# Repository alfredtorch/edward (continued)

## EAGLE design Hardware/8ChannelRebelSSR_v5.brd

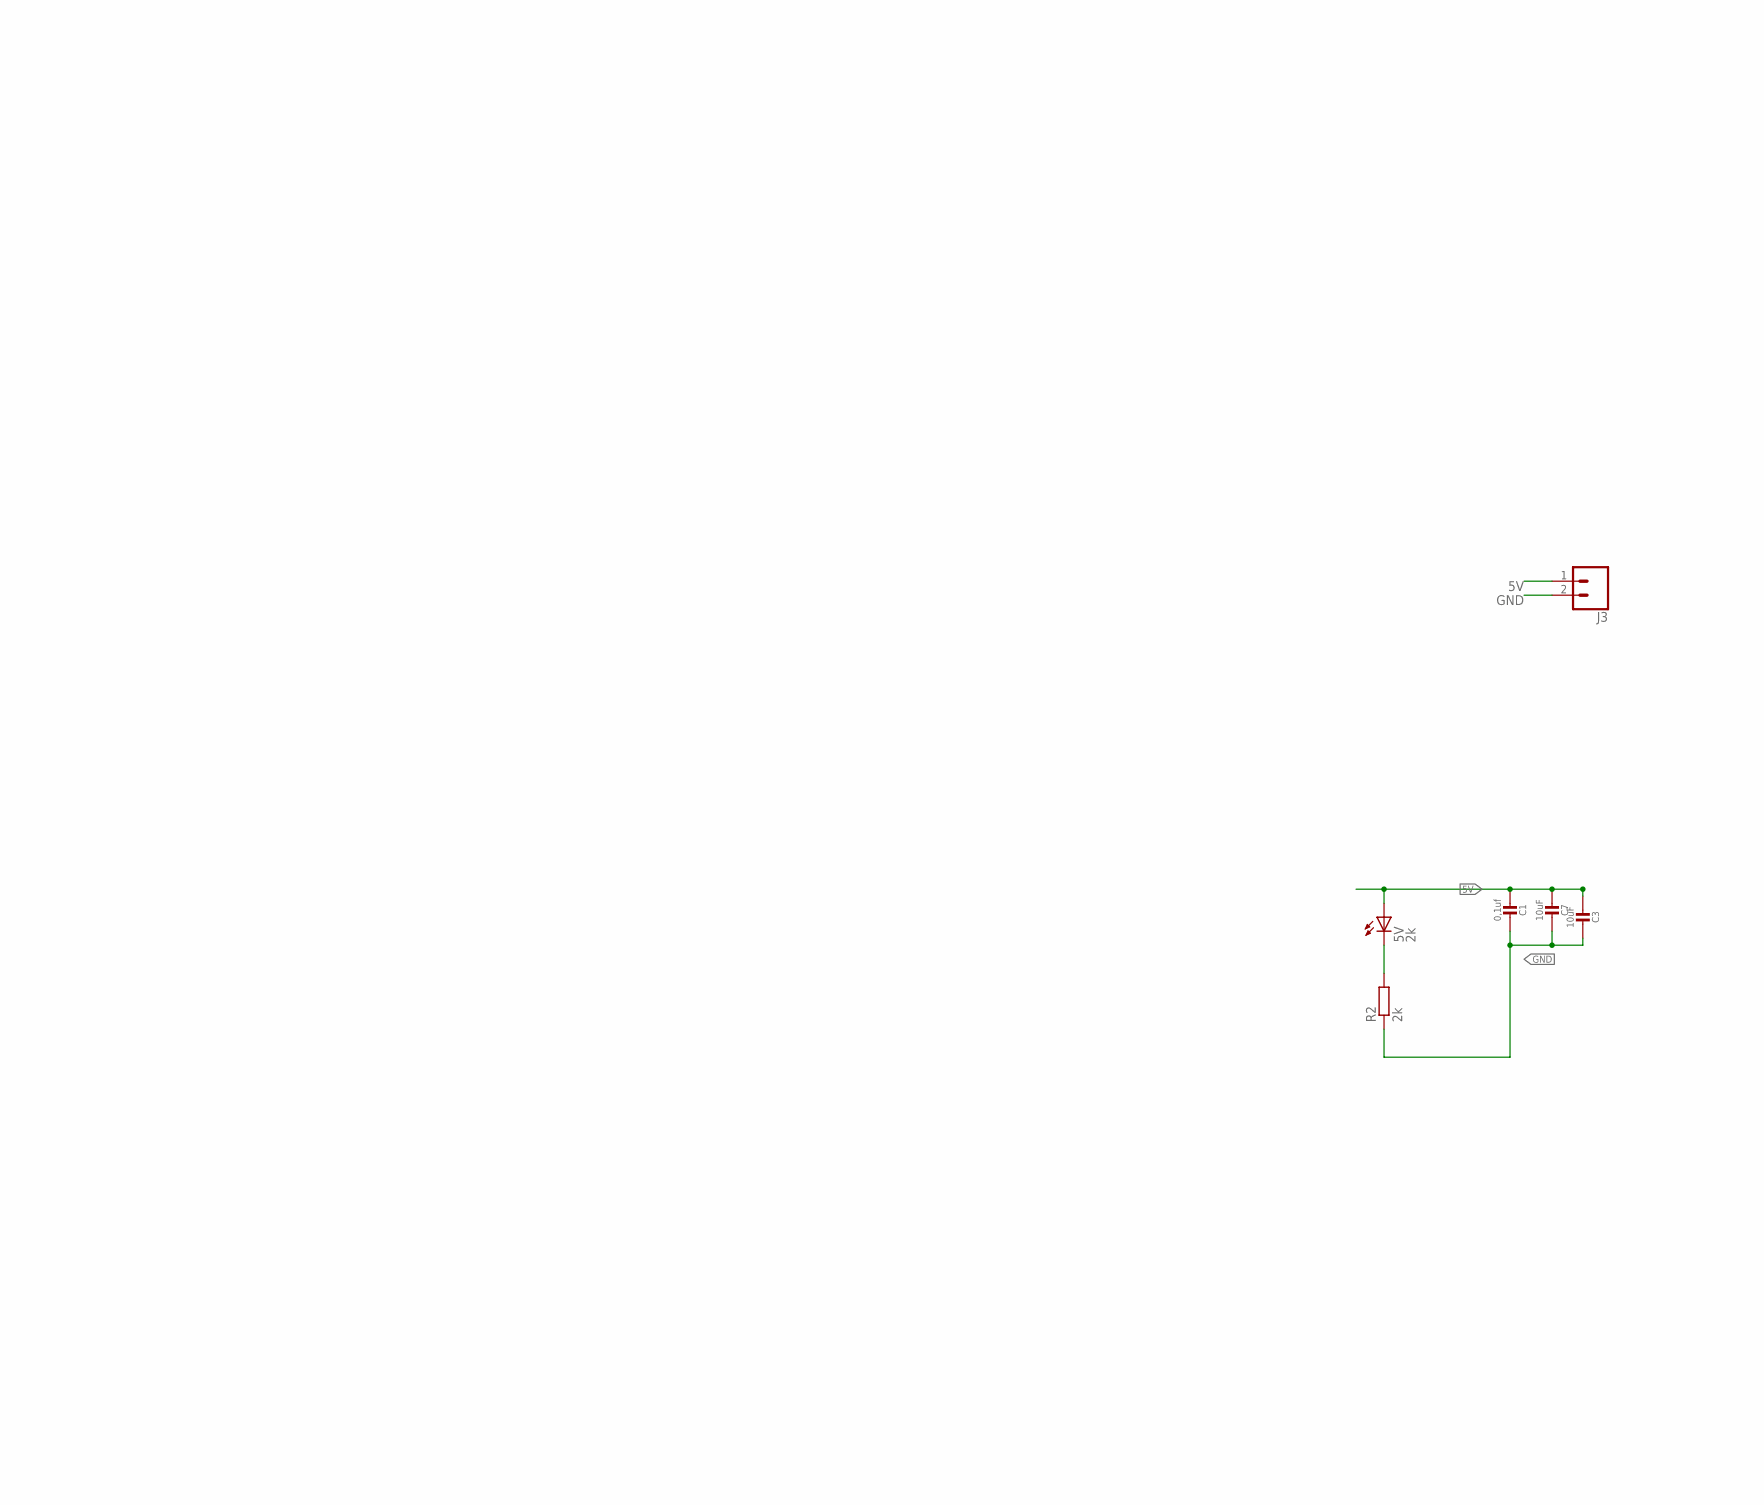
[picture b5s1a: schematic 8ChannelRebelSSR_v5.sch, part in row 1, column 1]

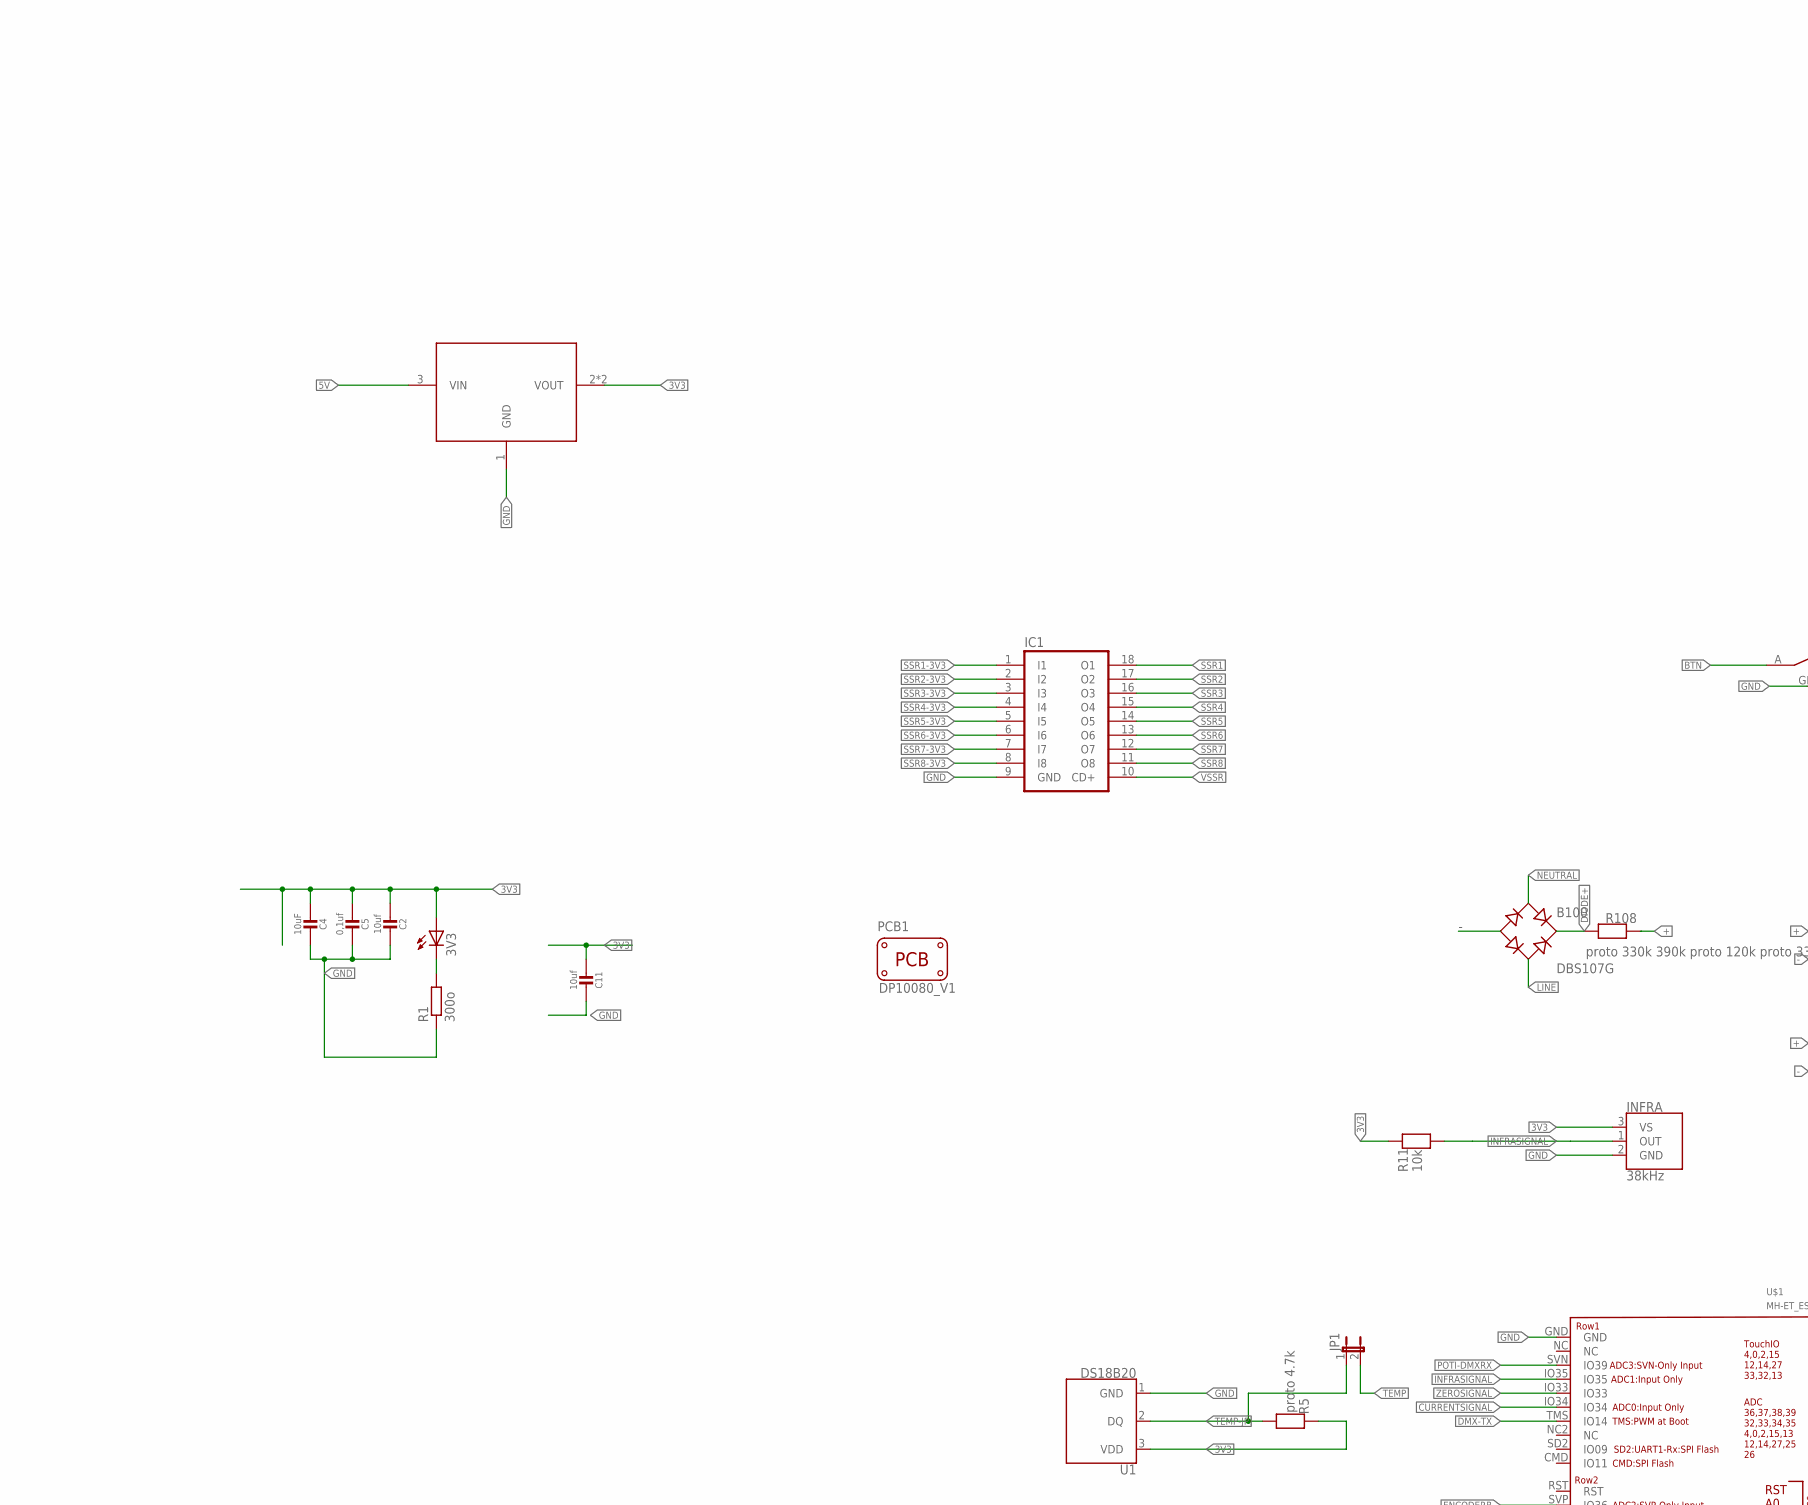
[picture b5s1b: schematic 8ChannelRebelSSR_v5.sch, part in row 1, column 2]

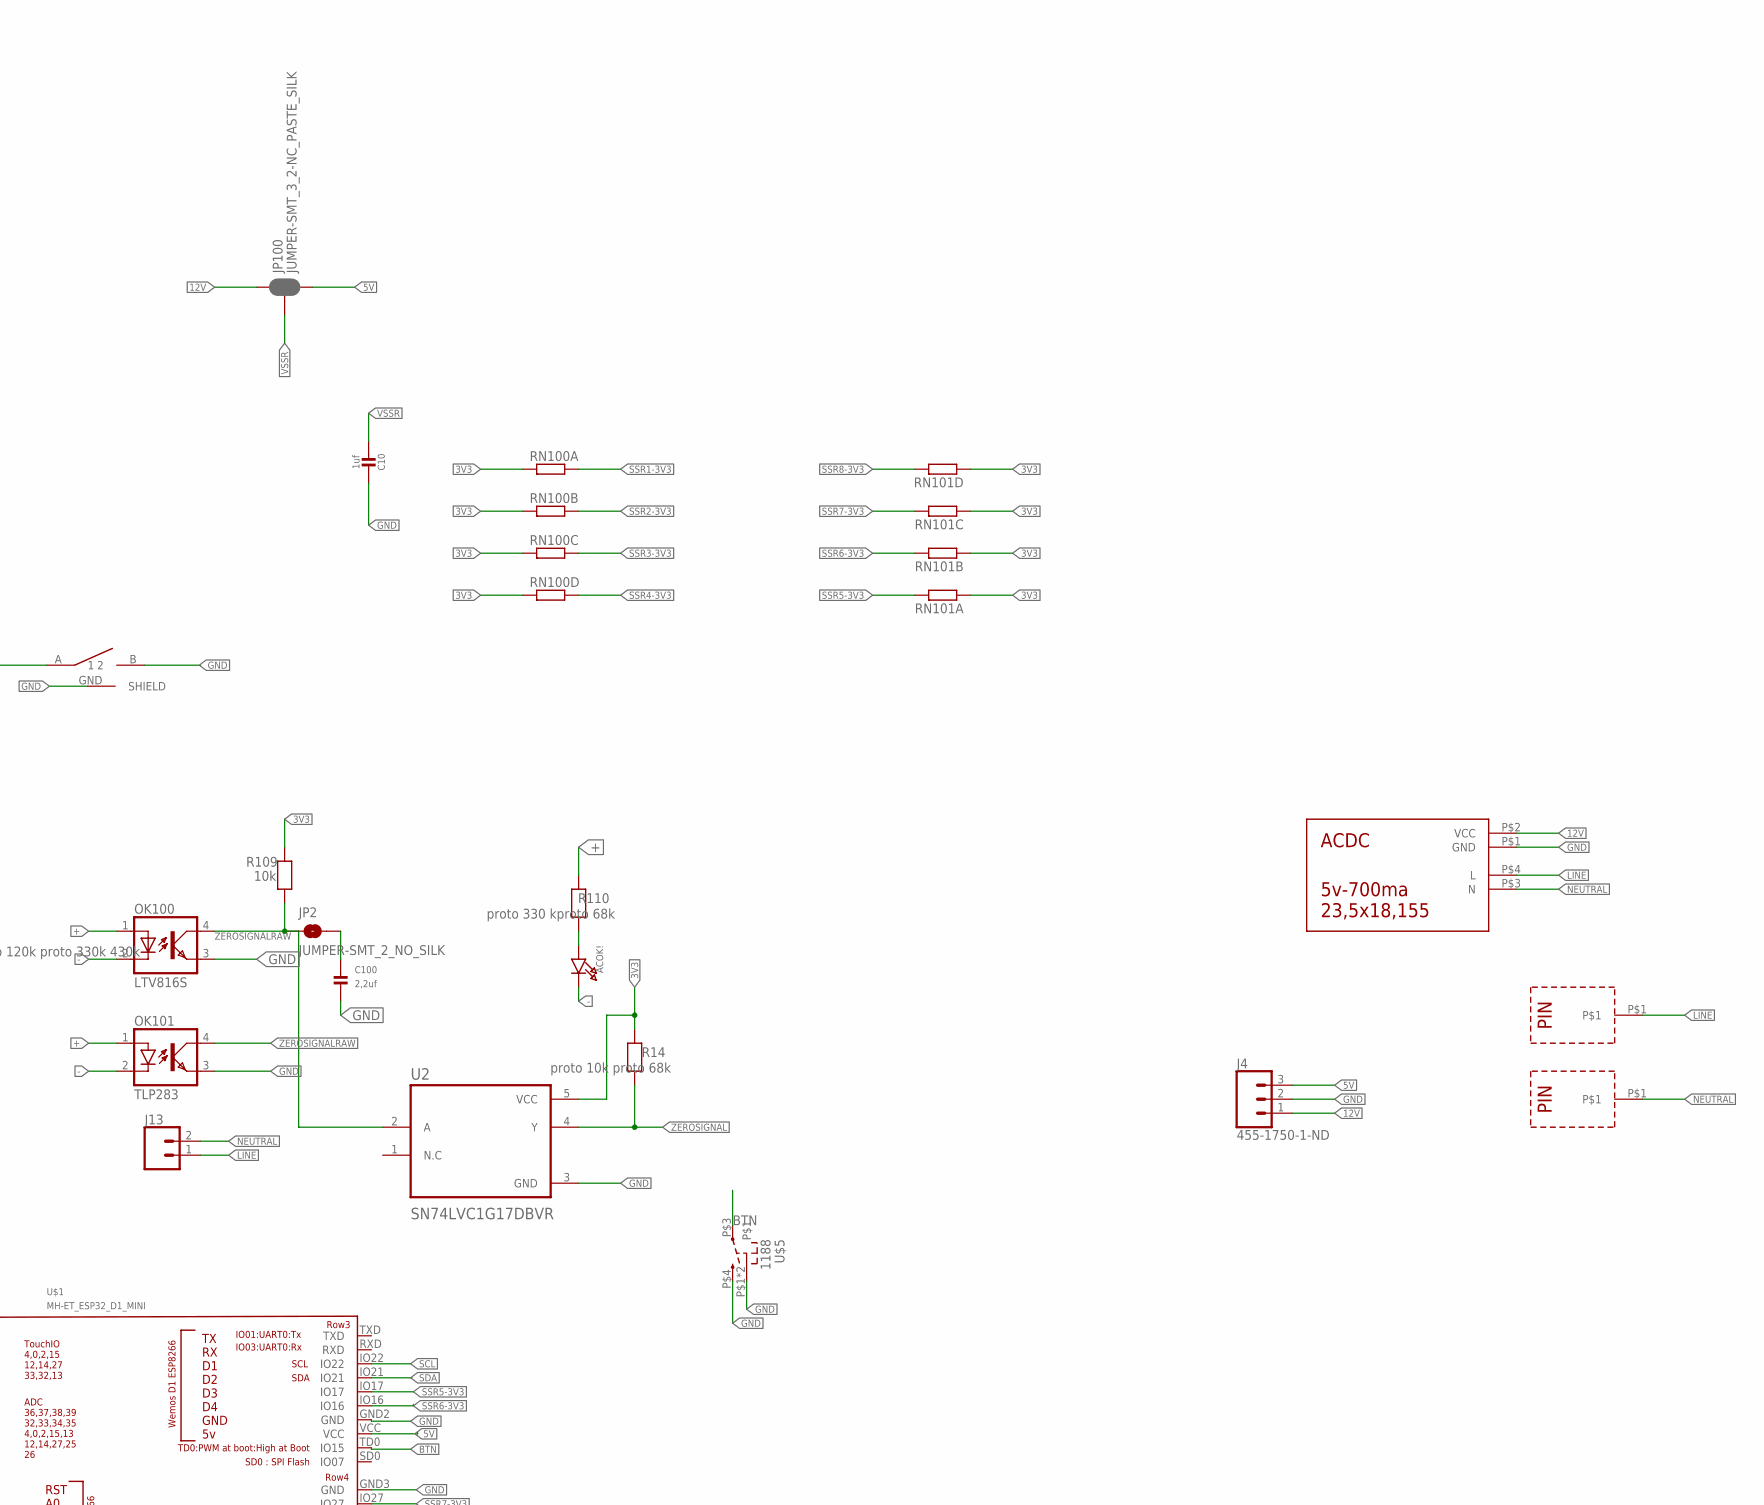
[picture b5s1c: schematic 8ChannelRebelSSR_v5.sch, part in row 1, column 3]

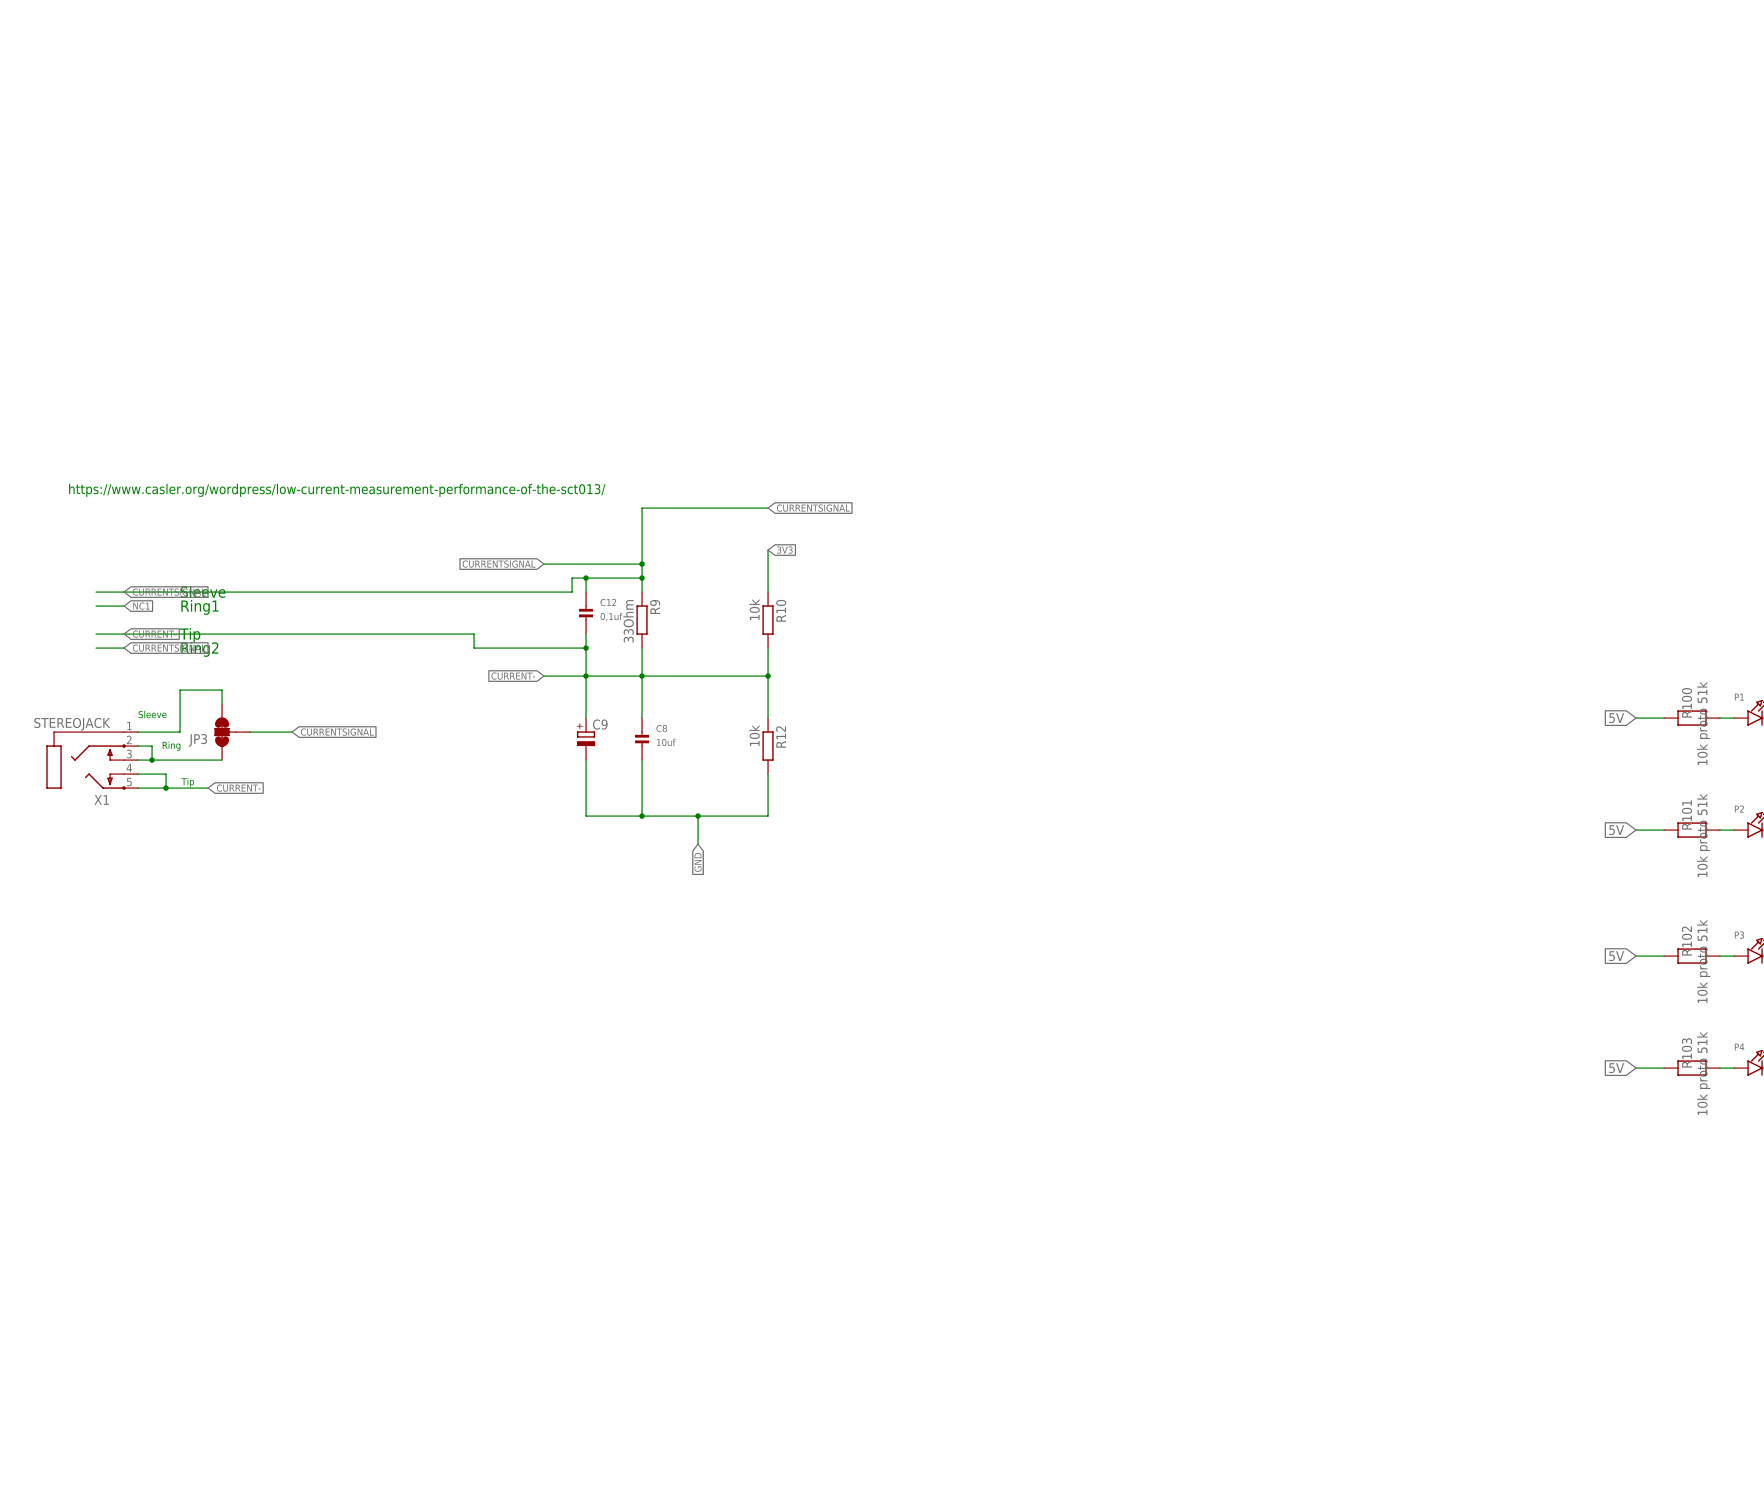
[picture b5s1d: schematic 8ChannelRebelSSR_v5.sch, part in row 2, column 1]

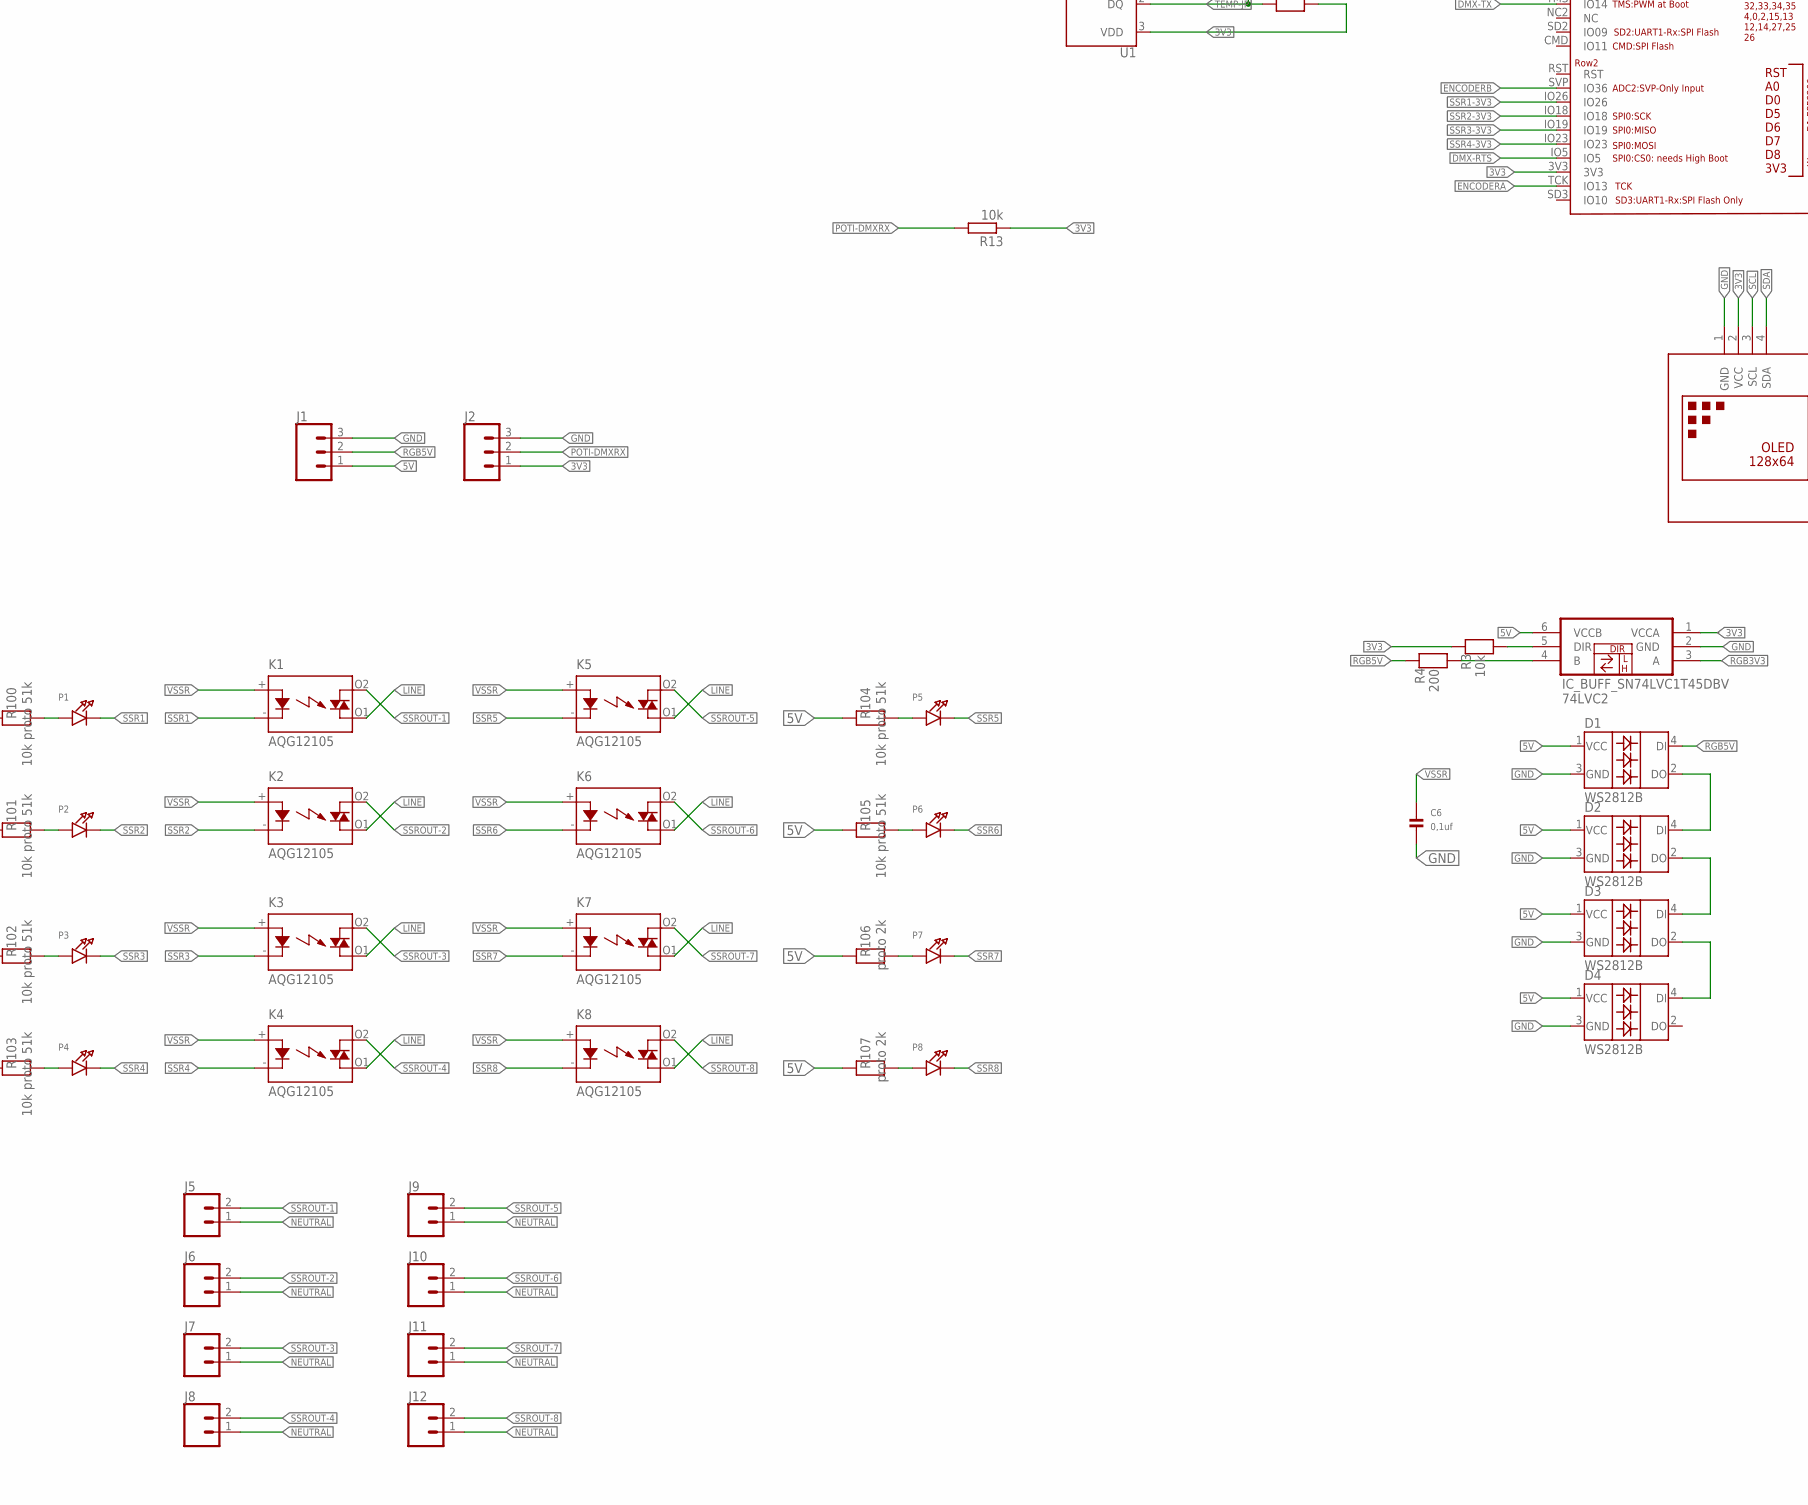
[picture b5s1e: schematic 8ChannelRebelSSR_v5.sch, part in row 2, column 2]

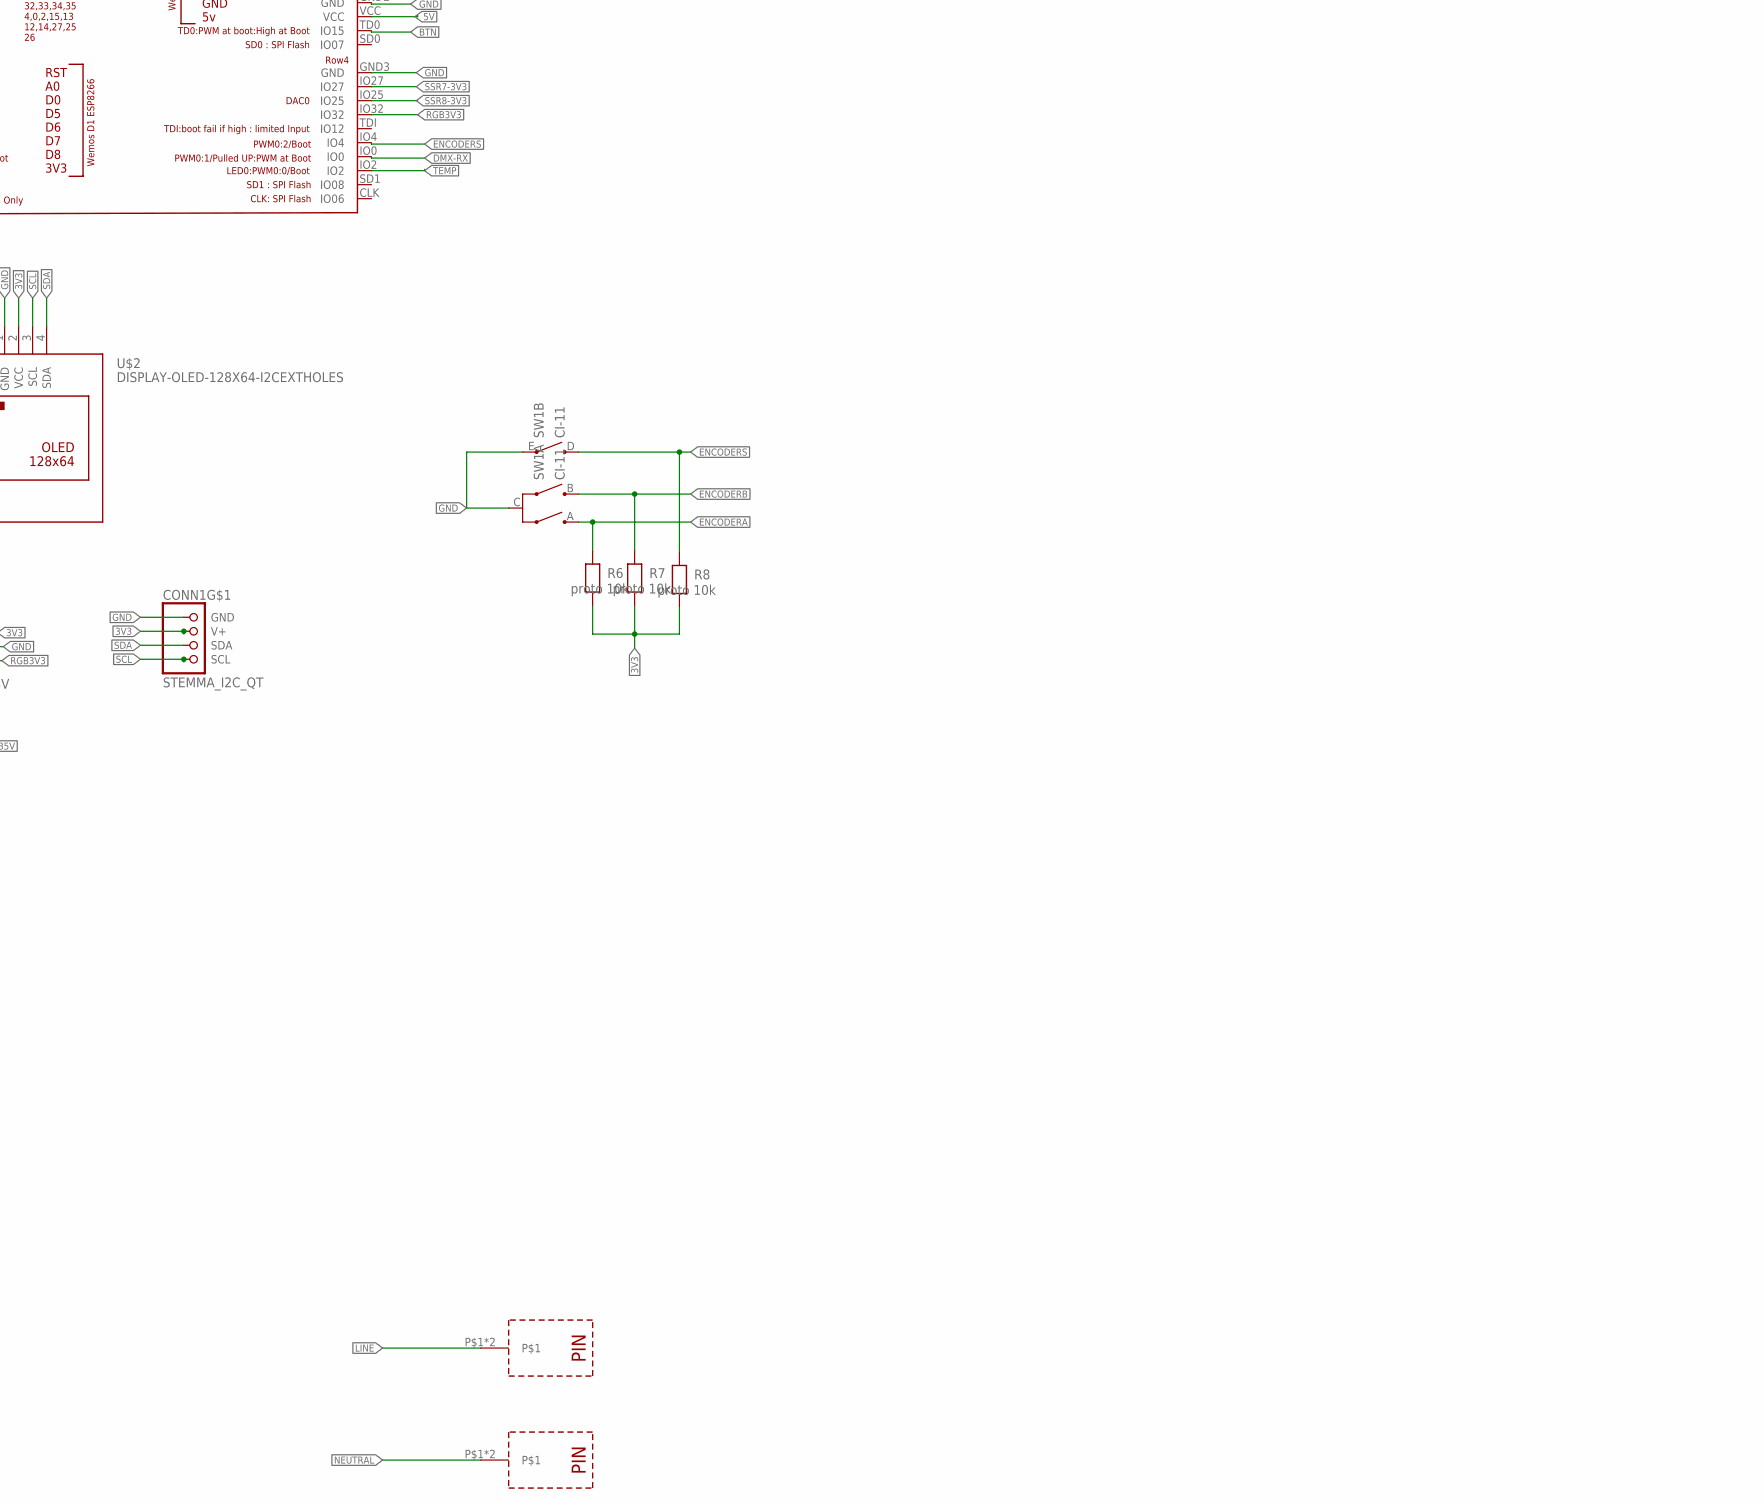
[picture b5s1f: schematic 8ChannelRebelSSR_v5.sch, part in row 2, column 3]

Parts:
3V3: LEDCHIPLED_0805; CHIPLED_0805
5V: 2k; CHIPLED_0805
74LVC2: IC_BUFF_SN74LVC1T45DBV; DBV-R-PDSO-G6
ACOK!: LED0805; CHIPLED_0805
B100: DBS107G; DBS
C1, C5: 0,1uf; 0805-NO
C2, C11: 10uf; 0805-NO
C3, C4, C7: 10uF; 0805-NO
C6, C12: 0,1uf; 0805_NOTHERMALS@1
C8: 10uf; 0805_NOTHERMALS@1
C9: CPOL-EUE1.8-4; E1,8-4
C10: 1uf; 0805-NO
C100: 2,2uf; 0805_NOTHERMALS@1
CONN1: STEMMA_I2C_QT; JST_SH4
D1, D2, D3, D4: WS2812B
IC1: IC_ULN2803ADW; SO-18L
INFRA: 38kHz; TSOP382
J1, J2: CONN_03POLAR; MOLEX-1X3
J3: CONN_02POLAR; MOLEX-1X2
J4: 455-1750-1-ND; 1X03
J5, J6, J7, J8, J9, J10, J11, J12, J13: CONN_023.5MM; SCREWTERMINAL-3.5MM-2
JP1: JUMPER2
JP2: JUMPER-SMT_2_NO_SILK; SMT-JUMPER_2_NO_SILK
JP3: JUMPER-PAD-3-NC_BY_TRACE; PAD-JUMPER-3-3OF3_NC_BY_TRACE_YES_SILK_FULL_BOX
JP100: JUMPER-SMT_3_2-NC_PASTE_SILK; SMT-JUMPER_3_2-NC_PASTE_SILK
K1, K2, K3, K4, K5, K6, K7, K8: AQG12105; AQG
OK100: LTV816S; DIL4-SMD
OK101: TLP283; MINI-FLAT-4
P1, P2, P3, P4, P5, P6, P7, P8: LED0805; CHIPLED_0805
PCB1: PCB_DP_RECTANGLE-80X100; DP10080_V1
R1: 300o; R805
R2: 2k; R805
R3, R11, R109: 10k; 0805@1
R4: 200; 0805@1
R5: proto 4.7k; 0805@1
R6, R7, R8: proto 10k; 0805@1
R9: 33Ohm; R805
R10, R12, R13: 10k; R805
R14: proto 10k proto 68k; 0805@1
R100, R101, R102, R103, R104, R105: 10k proto 51k; 0805@1
R106, R107: proto 2k; 0805@1
R108: proto 330k 390k proto 120k proto 330k 430k; 0805@1
R110: proto 330 kproto 68k; 0805@1
RN100, RN101: RESISTOR_ARRAY_4; RN8P-4R-CRA06S
SW1: CI-11
U1: DS18B20; TO-92-AMMO
U2: SN74LVC1G17DBVR; SOT95P280X145-5N
U$1: MH-ET_ESP32_D1_MINI
U$2: DISPLAY-OLED-128X64-I2CEXTHOLES; DISPLAY-OLED-128X64-MAX-I2C
U$4: SWITCH4.5-4,5; SWITCH4.5X4.5
U$5: 1188
U$6: AP11173V3; SOT223
U$7: ACDC-SUPPLY; ACDC-5V
U$15, U$17: EST026_COLDPRESSTERMINAL; EST026-COLDPRESSTERMINAL
U$16, U$18: SCREWTERMINAL_BLOCL5X5_FLAT; SCREWTERMINALFLAT5X5
X1: STEREOJACK; STX3100

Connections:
3V3: 3V3.A, 74LVC2.1 (VCCA), C2.2, C4.2, C5.2, C11.2, CONN1.2 (V+), INFRA.3 (VS), J2.1, R3.2, R5.2, R6.1, R7.1, R8.1, R10.1, R11.2, R13.1, R14.2, R109.2, RN100.1, RN100.2 (1), RN100.3 (1), RN100.4 (1), RN101.1, RN101.2 (1), RN101.3 (1), RN101.4 (1), U1.3 (VDD), U2.5 (VCC), U$1.3V3, U$2.2 (VCC), U$6.2 (VOUT), U$6.4 (VOUT)
5V: 5V.A, 74LVC2.6 (VCCB), C1.2, C3.2, C7.2, D1.1 (VCC), D2.1 (VCC), D3.1 (VCC), D4.1 (VCC), J1.1, J3.1, J4.3, JP100.3, R100.2, R101.2, R102.2, R103.2, R104.2, R105.2, R106.2, R107.2, U$1.VCC, U$6.3 (VIN)
12V: J4.1, JP100.1, U$7.P$2 (VCC)
+: OK100.1 (A), OK101.1 (A), R108.2, R110.2
-: ACOK!.C, B100.-, OK100.2 (C), OK101.2 (C)
BTN: U$1.TD0 (IO15), U$4.A (1), U$5.P$3 (1)
CURRENT-: C8.1, C9.+, C12.2, R9.2, R10.2, R12.1, X1.4, X1.5; also elsewhere on the board
CURRENTSIGNAL: C12.1, JP3.2, R9.1, U$1.IO34; also elsewhere on the board
DIODE+: B100.+, R108.1
DMX-RTS: U$1.IO5; also elsewhere on the board
DMX-RX: U$1.IO0
DMX-TX: U$1.TMS (IO14); also elsewhere on the board
ENCODERA: R6.2, SW1.A, U$1.TCK (IO13)
ENCODERB: R7.2, SW1.B, U$1.SVP (IO36)
ENCODERS: R8.2, SW1.D, U$1.IO4
GND: 74LVC2.2 (GND), C1.1, C2.1, C3.1, C4.1, C5.1, C6.2, C7.1, C8.2, C9.-, C10.1, C11.1, C100.2, CONN1.1 (GND), D1.3 (GND), D2.3 (GND), D3.3 (GND), D4.3 (GND), IC1.9 (GND), INFRA.2 (GND), J1.3, J2.3, J3.2, J4.2, OK100.3 (EMIT), OK101.3 (EMIT), R1.1, R2.1, R12.2, SW1.C, SW1.E, U1.1 (GND), U2.3 (GND), U$1.GND, U$1.GND2 (GND), U$1.GND3 (GND), U$2.1 (GND), U$4.B (2), U$4.GND (SHIELD), U$5.P$1, U$5.P$2, U$5.P$4 (3), U$6.1 (GND), U$7.P$1 (GND)
INFRASIGNAL: INFRA.1 (OUT), R11.1, U$1.IO35
LINE: B100.AC2, J13.1, K1.O1 (DS2), K2.O1 (DS2), K3.O1 (DS2), K4.O1 (DS2), K5.O1 (DS2), K6.O1 (DS2), K7.O1 (DS2), K8.O1 (DS2), U$7.P$4 (L), U$15.P$1, U$15.P$2, U$16.P$1
unnamed 18: C100.1, JP2.2; also elsewhere on the board
unnamed: 74LVC2.5 (DIR), R3.1
unnamed: 74LVC2.4 (B), R4.1
unnamed: D1.2 (DO), D2.4 (DI)
unnamed: D2.2 (DO), D3.4 (DI)
unnamed: D3.2 (DO), D4.4 (DI)
unnamed: ACOK!.A, R110.1
unnamed: 3V3.C, R1.2
unnamed: 5V.C, R2.2
unnamed: P4.A, R103.1
unnamed: P3.A, R102.1
unnamed: P2.A, R101.1
unnamed: P1.A, R100.1
unnamed: P8.A, R107.1
unnamed: P7.A, R106.1
unnamed: P6.A, R105.1
unnamed: P5.A, R104.1
NEUTRAL: B100.AC1, J5.1, J6.1, J7.1, J8.1, J9.1, J10.1, J11.1, J12.1, J13.2, U$7.P$3 (N), U$17.P$1, U$17.P$2, U$18.P$1
unnamed: JP3.1, X1.2, X1.3
unnamed: JP3.3, X1.1
POTI-DMXRX: J2.2, R13.2, U$1.SVN (IO39); also elsewhere on the board
RGB3V3: 74LVC2.3 (A), U$1.IO32
RGB5V: D1.4 (DI), J1.2, R4.2
SCL: CONN1.4 (SCL), U$1.IO22, U$2.3 (SCL)
SDA: CONN1.3 (SDA), U$1.IO21, U$2.4 (SDA)
SSR1: IC1.18 (O1), K1.- (K), P1.C
SSR1-3V3: IC1.1 (I1), RN100.8 (2), U$1.IO26
SSR2: IC1.17 (O2), K2.- (K), P2.C
SSR2-3V3: IC1.2 (I2), RN100.7 (2), U$1.IO18
SSR3: IC1.16 (O3), K3.- (K), P3.C
SSR3-3V3: IC1.3 (I3), RN100.6 (2), U$1.IO19
SSR4: IC1.15 (O4), K4.- (K), P4.C
SSR4-3V3: IC1.4 (I4), RN100.5 (2), U$1.IO23
SSR5: IC1.14 (O5), K5.- (K), P5.C
SSR5-3V3: IC1.5 (I5), RN101.8 (2), U$1.IO17
SSR6: IC1.13 (O6), K6.- (K), P6.C
SSR6-3V3: IC1.6 (I6), RN101.7 (2), U$1.IO16
SSR7: IC1.12 (O7), K7.- (K), P7.C
SSR7-3V3: IC1.7 (I7), RN101.6 (2), U$1.IO27
SSR8: IC1.11 (O8), K8.- (K), P8.C
SSR8-3V3: IC1.8 (I8), RN101.5 (2), U$1.IO25
SSROUT-1: J5.2, K1.O2 (DS1)
SSROUT-2: J6.2, K2.O2 (DS1)
SSROUT-3: J7.2, K3.O2 (DS1)
SSROUT-4: J8.2, K4.O2 (DS1)
SSROUT-5: J9.2, K5.O2 (DS1)
SSROUT-6: J10.2, K6.O2 (DS1)
SSROUT-7: J11.2, K7.O2 (DS1)
SSROUT-8: J12.2, K8.O2 (DS1)
TEMP: JP1.2, U$1.IO2
TEMP-JP: JP1.1, R5.1, U1.2 (DQ)
VSSR: C6.1, C10.2, IC1.10 (CD+), JP100.2, K1.+ (A), K2.+ (A), K3.+ (A), K4.+ (A), K5.+ (A), K6.+ (A), K7.+ (A), K8.+ (A)
ZEROSIGNAL: R14.1, U2.4 (Y), U$1.IO33
ZEROSIGNALRAW: JP2.1, OK100.4 (COL), OK101.4 (COL), R109.1, U2.2 (A); also elsewhere on the board

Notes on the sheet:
Sleeve
Ring1
Tip
Ring2
https://www.casler.org/wordpress/low-current-measurement-performance-of-the-sct013/
Ring

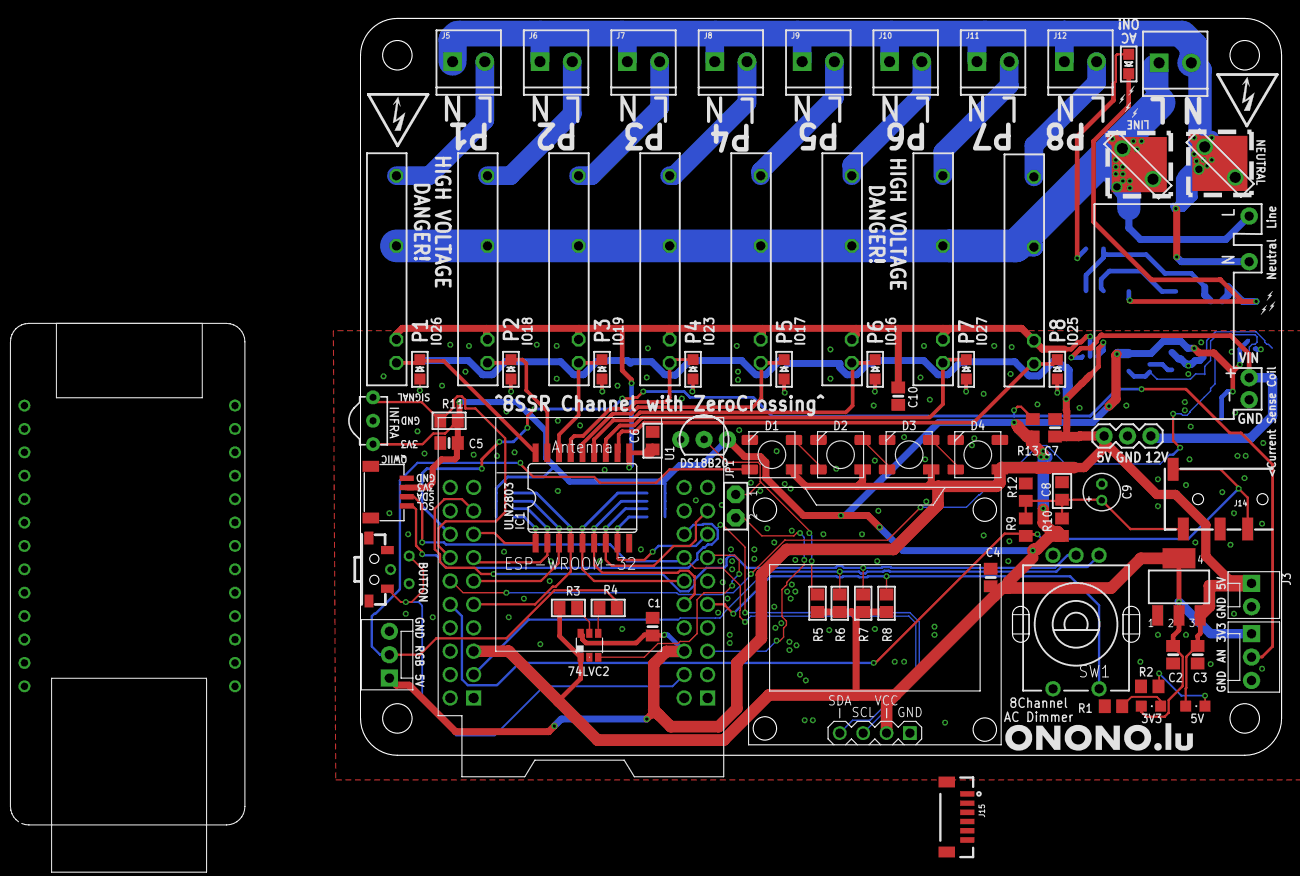
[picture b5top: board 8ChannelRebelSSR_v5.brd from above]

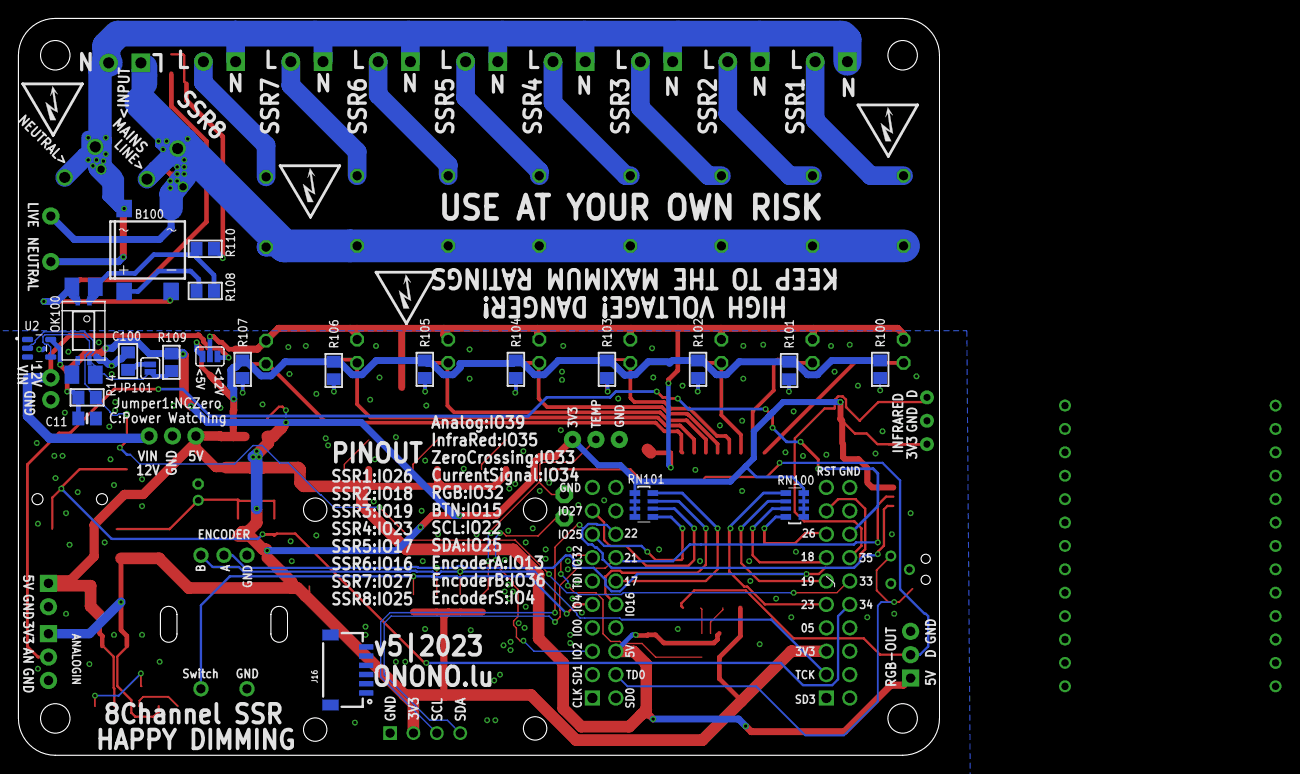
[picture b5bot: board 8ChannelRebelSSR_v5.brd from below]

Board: 2 copper layers, 100.0 x 80.0 mm, 111 parts (23 on the bottom side), 69 nets.

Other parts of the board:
J14: AUDIO_JACK_TRRSSMD_RA; AUDIO_JACK_3.5MM_TRRS_SMD_RA
J15: JST_6_PIN_VERTICAL; JST-6-SMD-VERT-1.0MM
J16: BM06B-SRSS-TB; JST-6-SMD-HORI-1.0MM
JP101: JUMPER-SMT_2_NO_SILK; SMT-JUMPER_2_NO_SILK
U$3: LOGOONONOLU_3MM_TOP
U$8, U$9, U$10, U$11, U$12, U$13, U$14: SPARKLOGO
U$19: W32-ETH01; WT32-ETH01-DIM

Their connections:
CURRENT-: J14.TIP; also elsewhere on the board
CURRENTSIGNAL: J14.EARTH, J14.RING2; also elsewhere on the board
DMX-RTS: J15.5; also elsewhere on the board
DMX-TX: J15.4; also elsewhere on the board
unnamed 18: JP101.2; also elsewhere on the board
POTI-DMXRX: J15.3; also elsewhere on the board
ZEROSIGNALRAW: JP101.1; also elsewhere on the board
